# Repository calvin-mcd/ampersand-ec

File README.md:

# ampersand ec

This an open-source, experimental 2-layer EC pcb for the Ampersand keyboard designed by whitefacemountain. Ampersand is a gummyworm mounted 13.5u keyboard with minimum 40s support needed.

The firmware has been adapted by whitefacemountain and is based on [cipulot](https://cipulot.squarespace.com/)'s Menhir firmware.

## Disclaimer:

*As the Ampersand case is designed for a MX pcb using an oring, this EC pcb requires the use of [EC naevies](https://keyboardtreehouse.com/products/naevies-ec-switches) switches. Other EC switches might only work with heavy modifications of the outer housings.*

## Layout

[Link](http://www.keyboard-layout-editor.com/#/gists/8dab2e8f328350c2c207f04be2b3e7d4)

There is currently only one naevies switch plate (7u, ansi, split right shift) available. More can be made available on request.

## To do

- [ ] order & test the revision (to eliminate an error with the bottom right control switch which is currently continuously triggered)

## Disclaimer

Please note that this project is a work in progress with no guarantees of a working outcome. No-one involved in this project is responsible for any usage issues that may arise. However, feel free to edit, modify and otherwise utilise these files.

## License

This project is released under the GPL v3 License. Please refer to the LICENCE file.

## Credits

As always big thanks also to the many people who inspired and helped with this board!

Any questions, contact Calvin0563 on Discord.

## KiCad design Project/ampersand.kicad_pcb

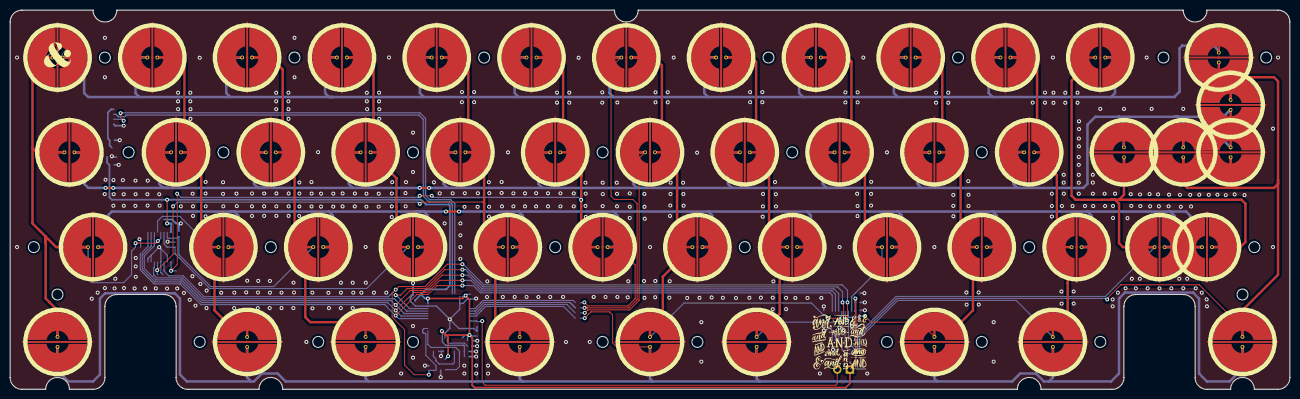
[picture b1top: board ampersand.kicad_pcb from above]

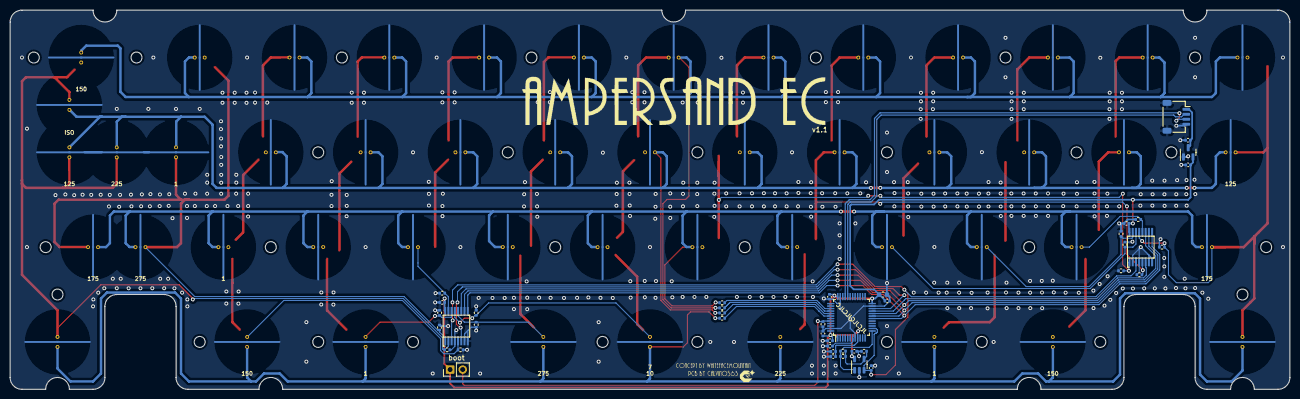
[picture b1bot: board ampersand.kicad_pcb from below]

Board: 2 copper layers, 257.2 x 76.2 mm, 121 parts (42 on the bottom side), 36 nets.

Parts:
C1, C2, C3, C4, C6, C8, C11, C12, C14: 100nF; C_0402_1005Metric
C5: 10uF; C_0603_1608Metric
C7, C9, C10: 1uF; C_0402_1005Metric
C13: 220pF NP0; C_0402_1005Metric
H1, H2, H3, H4, H5, H6, H7, H8, H9, H10, H11, H12, H13, H14, H15, H16, H17, H18, H19, H20, H21, H22, H23, H24, H25, H26, H27, H28, H29: MountingHole; HOLE_M2 (no arrow)
J1: JST SH; JST_SH_SM04B-SRSS-TB_1x04-1MP_P1.00mm_Horizontal
R1, R2, R3, R4: 100; R_0402_1005Metric
R5: 10k; R_0402_1005Metric
R6, R7, R8, R9, R10, R11, R14, R15, R16, R17, R18, R19, R20, R21: 100k; R_0402_1005Metric
R12: 1k; R_0402_1005Metric
R13: DNP; R_0402_1005Metric
SW1: DFU; PinHeader_1x02_P2.54mm_Vertical
SW_EC1, SW_EC2, SW_EC3, SW_EC4, SW_EC5, SW_EC6, SW_EC7, SW_EC8, SW_EC9, SW_EC10, SW_EC11, SW_EC12, SW_EC13, SW_EC14, SW_EC15, SW_EC16, SW_EC17, SW_EC18, SW_EC19, SW_EC20, SW_EC21, SW_EC22, SW_EC23, SW_EC24, SW_EC26, SW_EC27, SW_EC28, SW_EC29, SW_EC30, SW_EC31, SW_EC32, SW_EC33, SW_EC34, SW_EC35, SW_EC36, SW_EC37, SW_EC38, SW_EC39, SW_EC40, SW_EC41, SW_EC42, SW_EC43, SW_EC44, SW_EC45, SW_EC47, SW_EC48, SW_EC49, SW_EC50: Topre; ecs_pad_1U_no_ring
SW_EC25, SW_EC46: Topre; ecs_pad_1U_no_ring_1u_edge_cut
U1: STM32F072CBT6; LQFP-48_7x7mm_P0.5mm
U2: XC6206PxxxMR-Regulator_Linear; SOT-23
U3, U5: 74HC4051; TSSOP16
U4: OPA354; SOT-23-5

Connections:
+3V3: C1.1, C2.1, C3.1, C4.1, C5.1, C6.1, C7.1, C10.2, C11.2, C12.2, C14.2, SW1.1, U1.1 (VBAT), U1.9 (VDDA), U1.24 (VDD), U1.36 (VDDIO2), U1.48 (VDD), U2.2 (VO), U3.16 (VCC), U4.5 (V+), U5.16 (VCC)
+5V: C9.2, J1.1, U2.3 (VI)
ADC: R11.1, R13.1, U1.13 (PA3), U4.1
AMUX_SEL_0: U1.20 (PB2), U3.11 (S0), U5.11 (S0)
AMUX_SEL_1: U1.19 (PB1), U3.10 (S1), U5.10 (S1)
AMUX_SEL_2: U1.18 (PB0), U3.9 (S2), U5.9 (S2)
APLEX_EN_PIN_0: U1.21 (PB10), U3.6 (~E)
APLEX_EN_PIN_1: U1.22 (PB11), U5.6 (~E)
APLEX_OUT: C13.1, U1.14 (PA4), U3.3 (A), U4.3 (+), U5.3 (A)
BOOT0: R5.1, SW1.2, U1.44 (BOOT0)
COL0: R6.1, SW_EC1.1, SW_EC14.1, SW_EC27.1, SW_EC39.1, U3.13 (A0)
COL1: R9.1, SW_EC2.1, SW_EC15.1, SW_EC28.1, SW_EC40.1, U3.12 (A3)
COL2: R8.1, SW_EC3.1, SW_EC16.1, SW_EC29.1, SW_EC41.1, U3.15 (A2)
COL3: R7.1, SW_EC4.1, SW_EC17.1, SW_EC30.1, U3.14 (A1)
COL4: R10.1, SW_EC5.1, SW_EC18.1, SW_EC31.1, SW_EC43.1, U3.5 (A5)
COL5: R21.1, SW_EC6.1, SW_EC19.1, SW_EC32.1, U3.1 (A4)
COL6: R14.1, SW_EC7.1, SW_EC20.1, SW_EC33.1, SW_EC42.1, U5.13 (A0)
COL7: R17.1, SW_EC8.1, SW_EC21.1, SW_EC34.1, SW_EC45.1, U5.12 (A3)
COL8: R16.1, SW_EC9.1, SW_EC22.1, SW_EC35.1, U5.15 (A2)
COL9: R15.1, SW_EC10.1, SW_EC23.1, SW_EC36.1, SW_EC48.1, U5.14 (A1)
COL10: R18.1, SW_EC11.1, SW_EC24.1, SW_EC37.1, SW_EC49.1, U5.5 (A5)
COL11: R19.1, SW_EC12.1, SW_EC25.2, SW_EC38.1, SW_EC47.1, U5.1 (A4)
COL12: R20.1, SW_EC13.1, SW_EC26.1, SW_EC44.1, SW_EC46.1, SW_EC50.1, U5.2 (A6)
D_N: J1.2, U1.32 (PA11)
D_P: J1.3, U1.33 (PA12)
GND: C1.2, C2.2, C3.2, C4.2, C5.2, C6.2, C7.2, C8.2, C9.1, C10.1, C11.1, C12.1, C13.2, C14.1, J1.4, J1.MP (MountPin), R5.2, R6.2, R7.2, R8.2, R9.2, R10.2, R12.2, R14.2, R15.2, R16.2, R17.2, R18.2, R19.2, R20.2, R21.2, SW_EC1.3 (SG), SW_EC2.3 (SG), SW_EC3.3 (SG), SW_EC4.3 (SG), SW_EC5.3 (SG), SW_EC6.3 (SG), SW_EC7.3 (SG), SW_EC8.3 (SG), SW_EC9.3 (SG), SW_EC10.3 (SG), SW_EC11.3 (SG), SW_EC12.3 (SG), SW_EC13.3 (SG), SW_EC14.3 (SG), SW_EC15.3 (SG), SW_EC16.3 (SG), SW_EC17.3 (SG), SW_EC18.3 (SG), SW_EC19.3 (SG), SW_EC20.3 (SG), SW_EC21.3 (SG), SW_EC22.3 (SG), SW_EC23.3 (SG), SW_EC24.3 (SG), SW_EC25.3 (SG), SW_EC26.3 (SG), SW_EC27.3 (SG), SW_EC28.3 (SG), SW_EC29.3 (SG), SW_EC30.3 (SG), SW_EC31.3 (SG), SW_EC32.3 (SG), SW_EC33.3 (SG), SW_EC34.3 (SG), SW_EC35.3 (SG), SW_EC36.3 (SG), SW_EC37.3 (SG), SW_EC38.3 (SG), SW_EC39.3 (SG), SW_EC40.3 (SG), SW_EC41.3 (SG), SW_EC42.3 (SG), SW_EC43.3 (SG), SW_EC44.3 (SG), SW_EC45.3 (SG), SW_EC46.3 (SG), SW_EC47.3 (SG), SW_EC48.3 (SG), SW_EC49.3 (SG), SW_EC50.3 (SG), U1.8 (VSSA), U1.23 (VSS), U1.35 (VSS), U1.47 (VSS), U2.1 (GND), U3.2 (A6), U3.4 (A7), U3.7 (VEE), U3.8 (GND), U4.2 (V-), U5.4 (A7), U5.7 (VEE), U5.8 (GND)
NRST: C8.1, U1.7 (NRST)
unnamed: R4.1, U1.39 (PB3)
unnamed: R3.1, U1.40 (PB4)
unnamed: R2.1, U1.41 (PB5)
unnamed: R1.1, U1.42 (PB6)
unnamed: R11.2, R12.1, R13.2, U4.4 (-)
ROW0: R3.2, SW_EC1.2, SW_EC2.2, SW_EC3.2, SW_EC4.2, SW_EC5.2, SW_EC6.2, SW_EC7.2, SW_EC8.2, SW_EC9.2, SW_EC10.2, SW_EC11.2, SW_EC12.2, SW_EC13.2
ROW1: R2.2, SW_EC14.2, SW_EC15.2, SW_EC16.2, SW_EC17.2, SW_EC18.2, SW_EC19.2, SW_EC20.2, SW_EC21.2, SW_EC22.2, SW_EC23.2, SW_EC24.2, SW_EC25.1, SW_EC26.2, SW_EC44.2, SW_EC46.2
ROW2: R4.2, SW_EC27.2, SW_EC28.2, SW_EC29.2, SW_EC30.2, SW_EC31.2, SW_EC32.2, SW_EC33.2, SW_EC34.2, SW_EC35.2, SW_EC36.2, SW_EC37.2, SW_EC38.2, SW_EC47.2
ROW3: R1.2, SW_EC39.2, SW_EC40.2, SW_EC41.2, SW_EC42.2, SW_EC43.2, SW_EC45.2, SW_EC48.2, SW_EC49.2, SW_EC50.2

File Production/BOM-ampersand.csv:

Comment,Designator,Footprint,LCSC,Quantity
1k,R12,R_0402_1005Metric,C11702,1
OPA354,U4,SOT-23-5,C36384,1
220pF NP0,C13,C_0402_1005Metric,C1530,1
JST SH,J1,JST_SH_SM04B-SRSS-TB_1x04-1MP_P1.00mm_Horizontal,C160404,1
100,"R1,R2,R3,R4",R_0402_1005Metric,C25076,4
100k,"R10,R11,R14,R15,R16,R17,R18,R19,R20,R21,R6,R7,R8,R9",R_0402_1005Metric,C25741,14
10k,R5,R_0402_1005Metric,C25744,1
100nF,"C1,C11,C12,C14,C2,C3,C4,C6,C8",C_0402_1005Metric,C307331,9
1uF,"C10,C7,C9",C_0402_1005Metric,C52923,3
XC6206PxxxMR-Regulator_Linear,U2,SOT-23,C5446,1
74HC4051,"U3,U5",TSSOP16,C5645,2
STM32F072CBT6,U1,LQFP-48_7x7mm_P0.5mm,C81720,1
10uF,C5,C_0603_1608Metric,C96446,1

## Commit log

2024-01-04 initialise
2024-01-09 clean up
2024-01-13 plate work
2024-01-27 backup
2024-03-30 pcb & plate revisions & firmware
2024-03-31 bottom row change, plate update, firmware update
2024-05-30 update & backup
2025-02-20 updated production files
    naevies plate added
2025-03-01 production files update
2025-04-01 firmware update
2025-04-30 v1 production files
2025-05-02 update
    error fixing
2025-05-02 update production files
2025-05-05 V1 completed
